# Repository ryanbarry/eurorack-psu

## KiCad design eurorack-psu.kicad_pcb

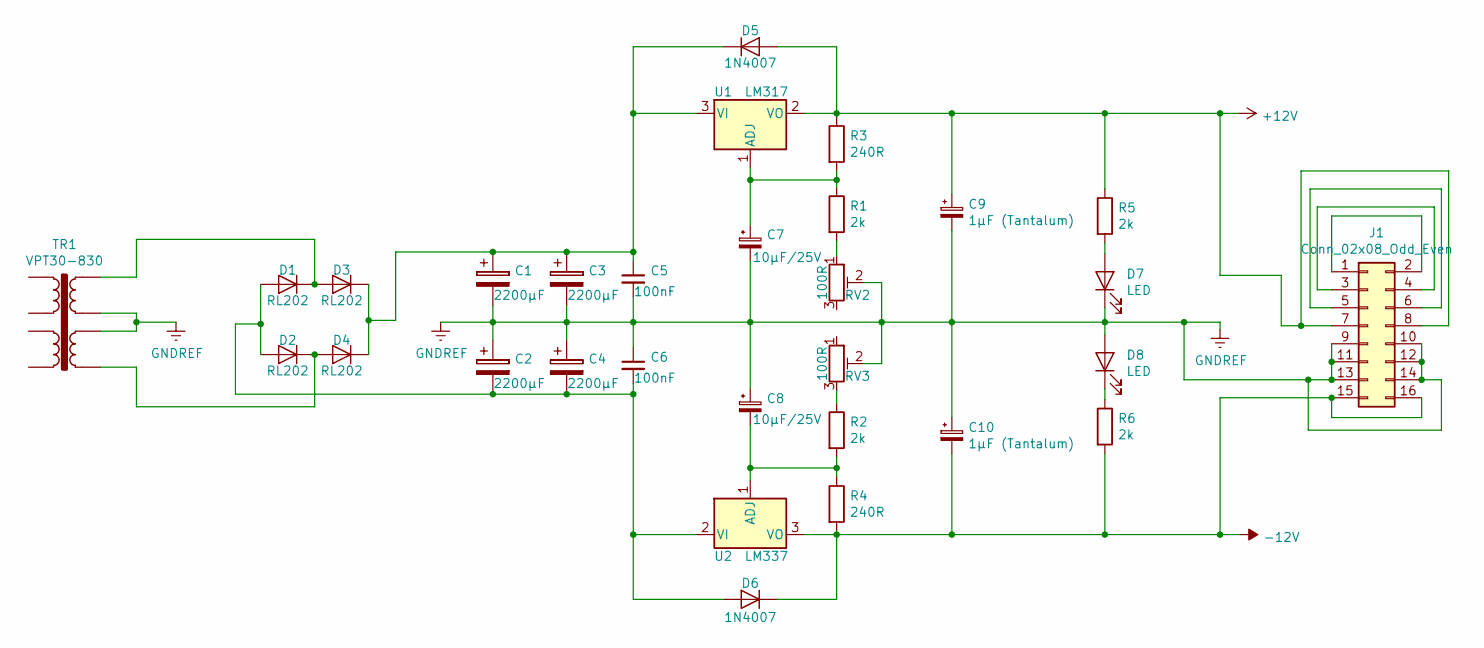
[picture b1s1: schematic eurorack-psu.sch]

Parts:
C1, C2, C3, C4: 2200µF; CP_Radial_D16.0mm_P7.50mm
C5, C6: 100nF; C_Disc_D4.3mm_W1.9mm_P5.00mm
C7, C8: 10µF/25V; CP_Radial_D5.0mm_P2.00mm
C9, C10: 1µF (Tantalum); CP_Radial_Tantal_D5.0mm_P5.00mm
D1, D2, D3, D4: RL202; D_DO-15_P5.08mm_Vertical_AnodeUp
D5, D6: 1N4007; D_DO-35_SOD27_P2.54mm_Vertical_KathodeUp
D7, D8: LED; LED_D3.0mm
J1: Conn_02x08_Odd_Even; Socket_Strip_Straight_2x08_Pitch2.54mm
R1, R2, R5, R6: 2k; R_Axial_DIN0207_L6.3mm_D2.5mm_P7.62mm_Horizontal
R3, R4: 240R; R_Axial_DIN0207_L6.3mm_D2.5mm_P7.62mm_Horizontal
RV2, RV3: 100R; Potentiometer_Trimmer_Bourns_3266P
TR1: VPT30-830; Transformer_Toroidal_D74.0mm_OffBoardMount
U1: LM317; TO-220
U2: LM337; TO-220

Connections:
+12V: C9.1, D5.2 (A), J1.7, J1.8, R3.1, R5.1, U1.2 (VO)
-12V: C10.2, D6.1 (K), J1.15, J1.16, R4.2, R6.2, U2.3 (VO)
GNDREF: C1.2, C2.1, C3.2, C4.1, C5.2, C6.1, C7.2, C8.1, C9.2, C10.1, D7.1 (K), D8.2 (A), J1.9, J1.10, J1.11, J1.12, J1.13, J1.14, RV2.2, RV3.1, RV3.2, TR1.6, TR1.7
unnamed: C1.1, C3.1, C5.1, D3.1 (K), D4.1 (K), D5.1 (K), U1.3 (VI)
unnamed: C2.2, C4.2, C6.2, D1.2 (A), D2.2 (A), D6.2 (A), U2.2 (VI)
unnamed: C7.1, R1.1, R3.2, U1.1 (ADJ)
unnamed: C8.2, R2.2, R4.1, U2.1 (ADJ)
unnamed: D1.1 (K), D3.2 (A), TR1.8
unnamed: D2.1 (K), D4.2 (A), TR1.5
unnamed: D7.2 (A), R5.2
unnamed: D8.1 (K), R6.1
unnamed: J1.1, J1.2
unnamed: J1.3, J1.4
unnamed: J1.5, J1.6
unnamed: R1.2, RV2.1
unnamed: R2.1, RV3.3

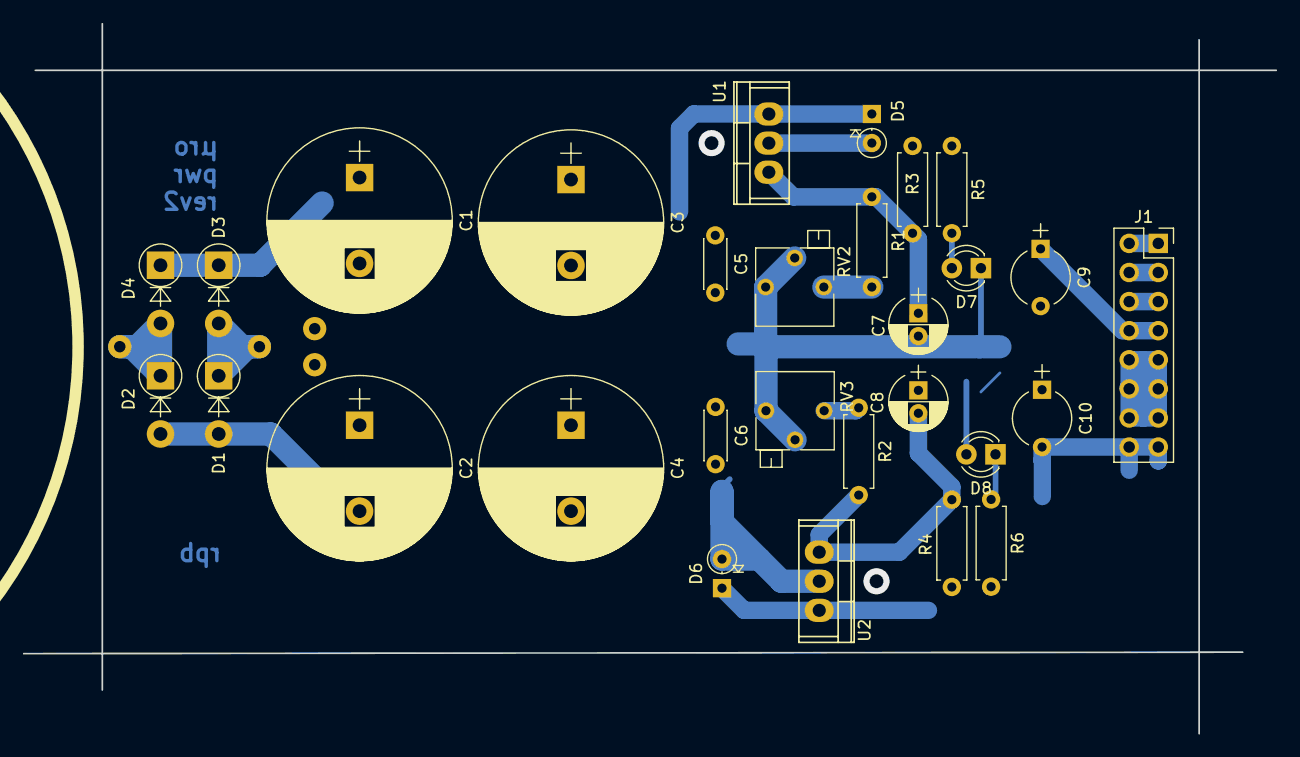
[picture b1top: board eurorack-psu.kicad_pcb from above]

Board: 2 copper layers, 109.3 x 62.0 mm, 30 parts (0 on the bottom side), 16 nets.

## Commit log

2018-11-16 rev1 of schematic, pcb, and fabrication
2018-11-16 make holes bigger for txfmr leads
2018-11-16 use new txfmr footprint, move trimmers further apart
    the trimmers were colliding (footprint outline is too small) and txfmr
    leads are too thick to fit through the default sized vias
2018-11-16 use larger minimum trace size for more reliable engraving
2018-11-17 rev2 pcb design w/ copper graphics and fabrication files
2019-04-25 rm oshw mark, tweak some stuff
